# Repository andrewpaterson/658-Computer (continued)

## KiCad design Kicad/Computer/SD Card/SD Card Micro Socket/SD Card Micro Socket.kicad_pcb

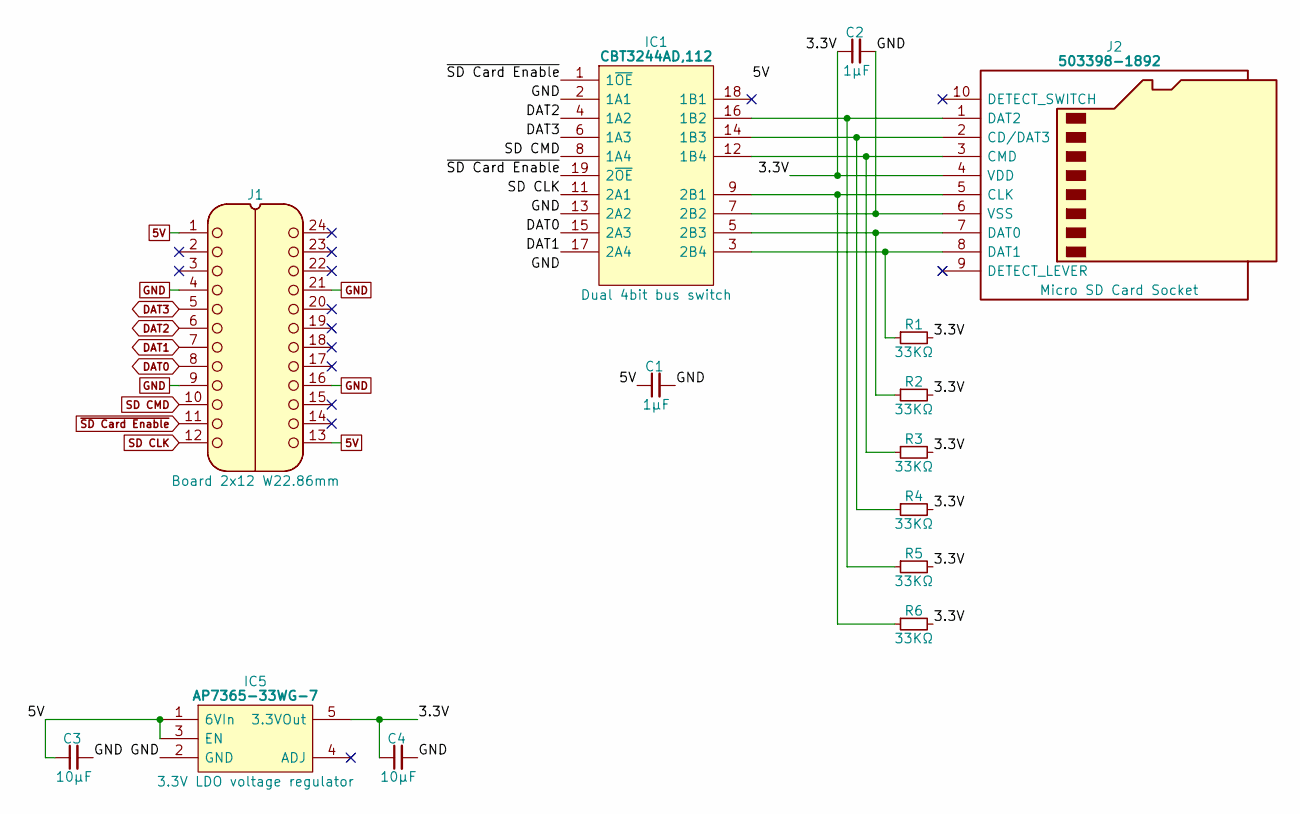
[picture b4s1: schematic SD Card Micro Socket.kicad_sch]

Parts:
C1, C2: 1μF; C_0805
C3, C4: 10µF; C_0805
IC1: CBT3244AD,112; SOIC127P1032X265-20N; Manufacturer_Part_Number CBT3244AD,112; Mouser Part Number 771-CBT3244AD
IC5: AP7365-33WG-7; SOT95P285X130-5N; Manufacturer_Part_Number AP7365-33WG-7; Mouser Part Number 621-AP7365-33WG-7
J1: Board 2x12 W22.86mm; DIP-24_Board_W22.86mm
J2: 503398-1892; Mouser2 Part Number 538-503398-1892
R1, R2, R3, R4, R5, R6: 33KΩ; R_0805

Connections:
5V: C1.1, C3.1, IC1.20 (5V), IC5.1 (6VIn), IC5.3 (EN), J1.1, J1.13
/3.3V: C2.1, C4.1, IC5.5 (3.3VOut), J2.4 (VDD), R1.2, R2.2, R3.2, R4.2, R5.2, R6.2
DAT0: IC1.15 (2A3), J1.8
DAT1: IC1.17 (2A4), J1.7
DAT2: IC1.4 (1A2), J1.6
DAT3: IC1.6 (1A3), J1.5
GND: C1.2, C2.2, C3.2, C4.2, IC1.2 (1A1), IC1.7 (2B2), IC1.10 (GND), IC1.13 (2A2), IC5.2 (GND), J1.4, J1.9, J1.16, J1.21, J2.6 (VSS)
unnamed: IC1.16 (1B2), J2.1 (DAT2), R5.1
unnamed: IC1.14 (1B3), J2.2 (CD/DAT3), R4.1
unnamed: IC1.12 (1B4), J2.3 (CMD), R3.1
unnamed: IC1.9 (2B1), J2.5 (CLK), R6.1
unnamed: IC1.5 (2B3), J2.7 (DAT0), R2.1
unnamed: IC1.3 (2B4), J2.8 (DAT1), R1.1
SD CLK: IC1.11 (2A1), J1.12
SD CMD: IC1.8 (1A4), J1.10
~SD Card Enable: IC1.1 (1~OE), IC1.19 (2~OE), J1.11

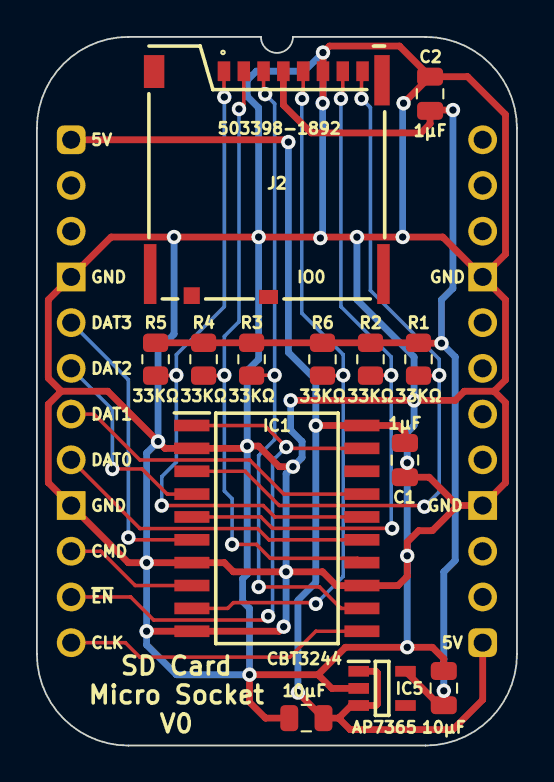
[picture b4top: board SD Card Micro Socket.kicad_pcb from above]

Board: 2 copper layers, 26.7 x 39.4 mm, 14 parts (0 on the bottom side), 16 nets.

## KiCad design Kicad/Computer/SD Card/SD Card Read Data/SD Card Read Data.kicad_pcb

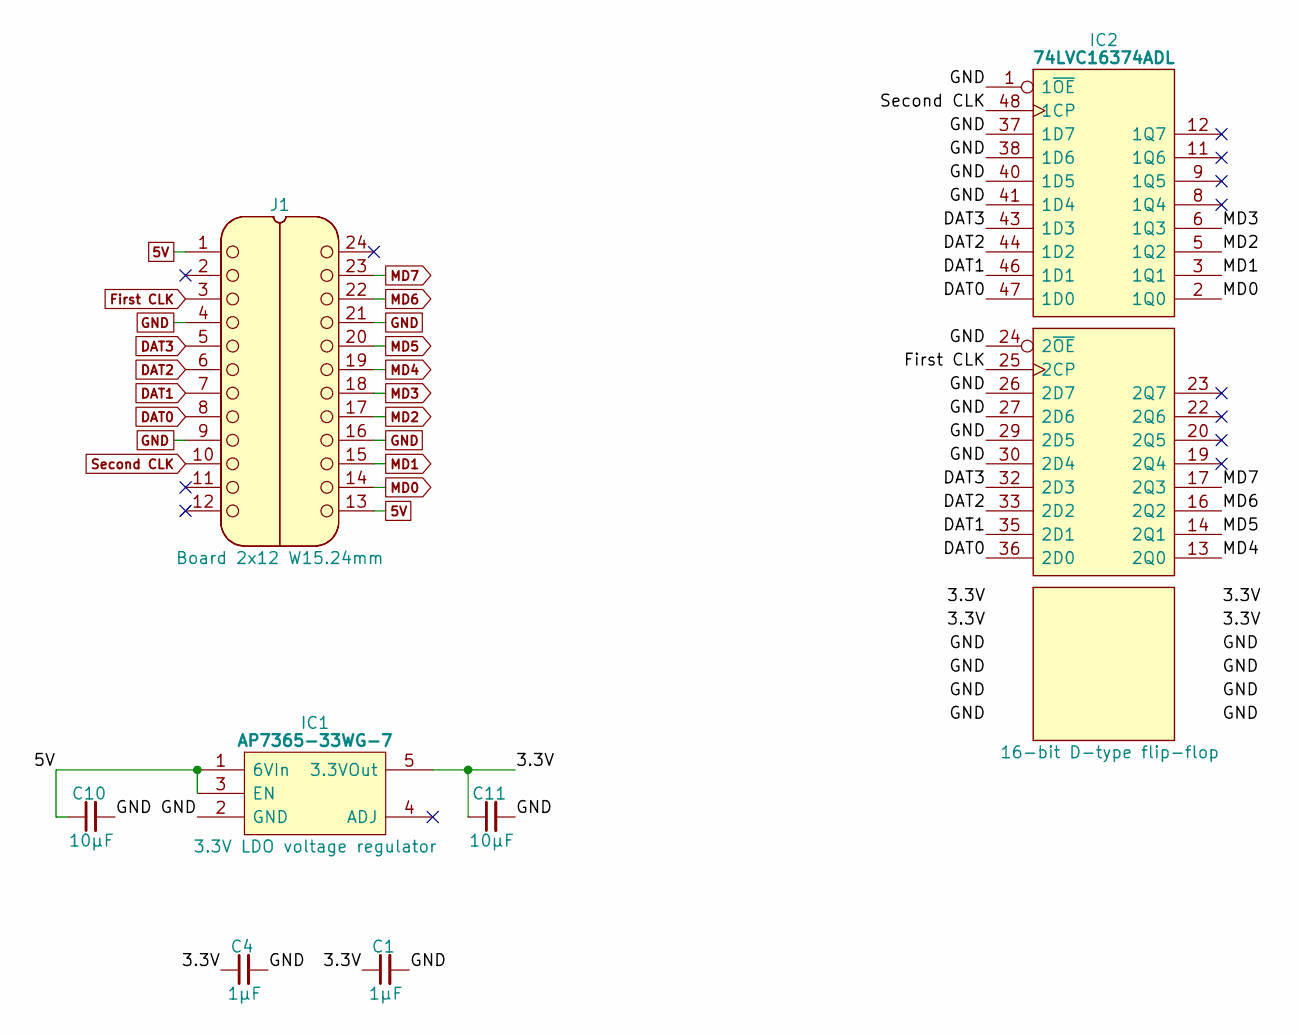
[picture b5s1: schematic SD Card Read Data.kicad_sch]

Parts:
C1, C4: 1μF; C_0805
C10, C11: 10μF; C_0805
IC1: AP7365-33WG-7; SOT95P285X130-5N; Manufacturer_Part_Number AP7365-33WG-7; Mouser Part Number 621-AP7365-33WG-7
IC2: 74LVC16374ADL; SOP64P1025X280-48N; Manufacturer_Part_Number 74LVC16374ADL; Mouser Part Number 771-74LVC16374ADL
J1: Board 2x12 W15.24mm; DIP-24_Board_W15.24mm

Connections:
5V: C10.1, IC1.1 (6VIn), IC1.3 (EN), J1.1, J1.13
/3.3V: C1.1, C4.1, C11.1, IC1.5 (3.3VOut), IC2.7 (3V), IC2.18 (3V), IC2.31 (3V), IC2.42 (3V)
DAT0: IC2.36 (2D0), IC2.47 (1D0), J1.8
DAT1: IC2.35 (2D1), IC2.46 (1D1), J1.7
DAT2: IC2.33 (2D2), IC2.44 (1D2), J1.6
DAT3: IC2.32 (2D3), IC2.43 (1D3), J1.5
First CLK: IC2.25 (2CP), J1.3
GND: C1.2, C4.2, C10.2, C11.2, IC1.2 (GND), IC2.1 (1~OE), IC2.4 (GND), IC2.10 (GND), IC2.15 (GND), IC2.21 (GND), IC2.24 (2~OE), IC2.26 (2D7), IC2.27 (2D6), IC2.28 (GND), IC2.29 (2D5), IC2.30 (2D4), IC2.34 (GND), IC2.37 (1D7), IC2.38 (1D6), IC2.39 (GND), IC2.40 (1D5), IC2.41 (1D4), IC2.45 (GND), J1.4, J1.9, J1.16, J1.21
MD0: IC2.2 (1Q0), J1.14
MD1: IC2.3 (1Q1), J1.15
MD2: IC2.5 (1Q2), J1.17
MD3: IC2.6 (1Q3), J1.18
MD4: IC2.13 (2Q0), J1.19
MD5: IC2.14 (2Q1), J1.20
MD6: IC2.16 (2Q2), J1.22
MD7: IC2.17 (2Q3), J1.23
Second CLK: IC2.48 (1CP), J1.10

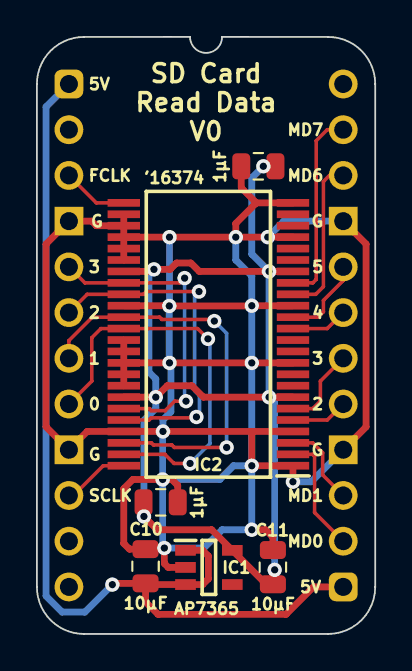
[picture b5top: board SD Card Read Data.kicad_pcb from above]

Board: 2 copper layers, 18.8 x 33.2 mm, 7 parts (0 on the bottom side), 17 nets.

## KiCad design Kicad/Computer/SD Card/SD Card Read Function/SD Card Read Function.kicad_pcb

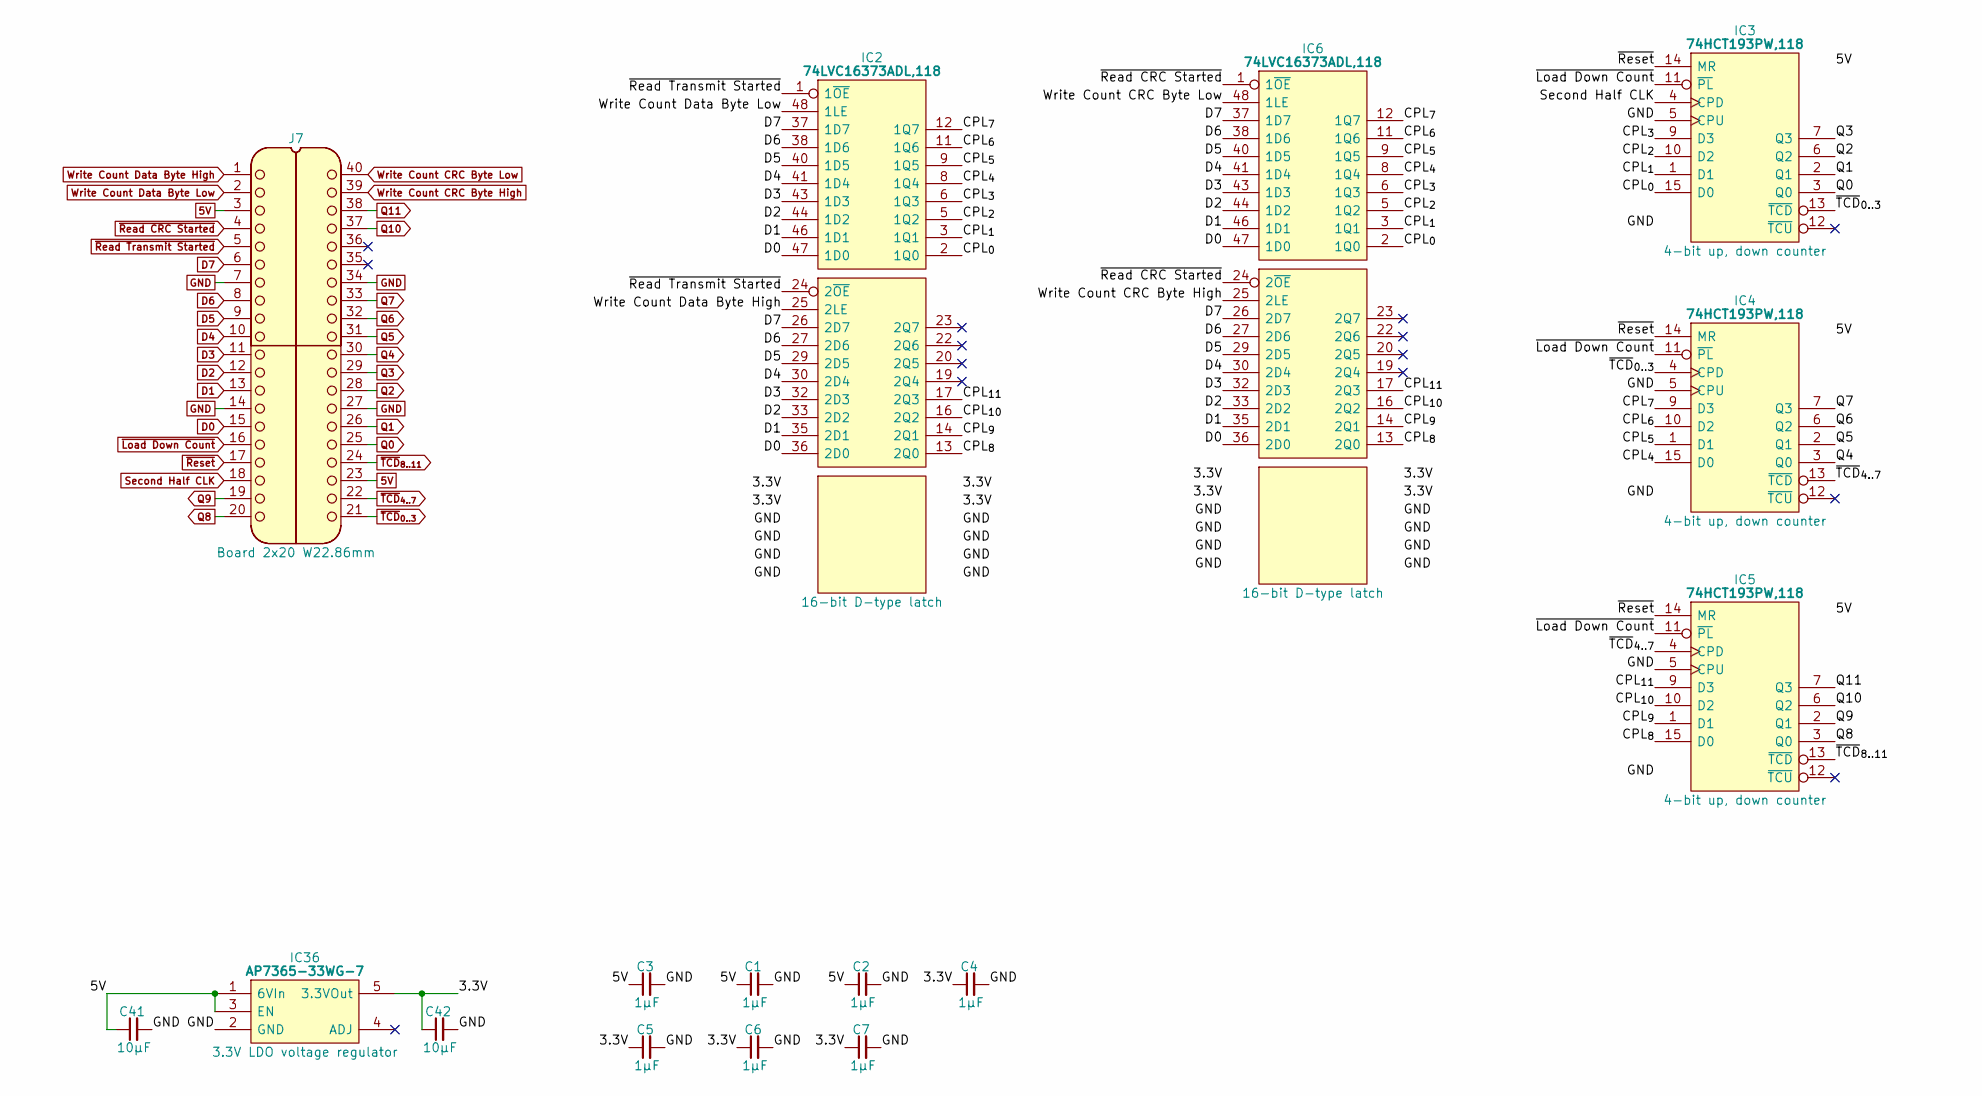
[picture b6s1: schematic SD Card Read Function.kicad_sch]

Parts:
C1, C2, C3, C4, C5, C6, C7: 1μF; C_0805
C41, C42: 10μF; C_0805
IC2, IC6: 74LVC16373ADL,118; SOP64P1025X280-48N; Mouser Part Number 771-LVC16373ADL118
IC3, IC4, IC5: 74HCT193PW,118; SOP65P640X110-16N; Manufacturer_Part_Number 74HCT193PW,118; Mouser Part Number 771-HCT193PW118
IC36: AP7365-33WG-7; SOT95P285X130-5N; Manufacturer_Part_Number AP7365-33WG-7; Mouser Part Number 621-AP7365-33WG-7
J7: Board 2x20 W22.86mm; DIP-40_Board_W22.86mm

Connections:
5V: C1.1, C2.1, C3.1, C41.1, IC3.16 (5V), IC4.16 (5V), IC5.16 (5V), IC36.1 (6VIn), IC36.3 (EN), J7.3, J7.23
/3.3V: C4.1, C5.1, C6.1, C7.1, C42.1, IC2.7 (3V), IC2.18 (3V), IC2.31 (3V), IC2.42 (3V), IC6.7 (3V), IC6.18 (3V), IC6.31 (3V), IC6.42 (3V), IC36.5 (3.3VOut)
/CPL_{0}: IC2.2 (1Q0), IC3.15 (D0), IC6.2 (1Q0)
/CPL_{1}: IC2.3 (1Q1), IC3.1 (D1), IC6.3 (1Q1)
/CPL_{2}: IC2.5 (1Q2), IC3.10 (D2), IC6.5 (1Q2)
/CPL_{3}: IC2.6 (1Q3), IC3.9 (D3), IC6.6 (1Q3)
/CPL_{4}: IC2.8 (1Q4), IC4.15 (D0), IC6.8 (1Q4)
/CPL_{5}: IC2.9 (1Q5), IC4.1 (D1), IC6.9 (1Q5)
/CPL_{6}: IC2.11 (1Q6), IC4.10 (D2), IC6.11 (1Q6)
/CPL_{7}: IC2.12 (1Q7), IC4.9 (D3), IC6.12 (1Q7)
/CPL_{8}: IC2.13 (2Q0), IC5.15 (D0), IC6.13 (2Q0)
/CPL_{9}: IC2.14 (2Q1), IC5.1 (D1), IC6.14 (2Q1)
/CPL_{10}: IC2.16 (2Q2), IC5.10 (D2), IC6.16 (2Q2)
/CPL_{11}: IC2.17 (2Q3), IC5.9 (D3), IC6.17 (2Q3)
D0: IC2.36 (2D0), IC2.47 (1D0), IC6.36 (2D0), IC6.47 (1D0), J7.15
D1: IC2.35 (2D1), IC2.46 (1D1), IC6.35 (2D1), IC6.46 (1D1), J7.13
D2: IC2.33 (2D2), IC2.44 (1D2), IC6.33 (2D2), IC6.44 (1D2), J7.12
D3: IC2.32 (2D3), IC2.43 (1D3), IC6.32 (2D3), IC6.43 (1D3), J7.11
D4: IC2.30 (2D4), IC2.41 (1D4), IC6.30 (2D4), IC6.41 (1D4), J7.10
D5: IC2.29 (2D5), IC2.40 (1D5), IC6.29 (2D5), IC6.40 (1D5), J7.9
D6: IC2.27 (2D6), IC2.38 (1D6), IC6.27 (2D6), IC6.38 (1D6), J7.8
D7: IC2.26 (2D7), IC2.37 (1D7), IC6.26 (2D7), IC6.37 (1D7), J7.6
GND: C1.2, C2.2, C3.2, C4.2, C5.2, C6.2, C7.2, C41.2, C42.2, IC2.4 (GND), IC2.10 (GND), IC2.15 (GND), IC2.21 (GND), IC2.28 (GND), IC2.34 (GND), IC2.39 (GND), IC2.45 (GND), IC3.5 (CPU), IC3.8 (GND), IC4.5 (CPU), IC4.8 (GND), IC5.5 (CPU), IC5.8 (GND), IC6.4 (GND), IC6.10 (GND), IC6.15 (GND), IC6.21 (GND), IC6.28 (GND), IC6.34 (GND), IC6.39 (GND), IC6.45 (GND), IC36.2 (GND), J7.7, J7.14, J7.27, J7.34
Q0: IC3.3 (Q0), J7.25
Q1: IC3.2 (Q1), J7.26
Q2: IC3.6 (Q2), J7.28
Q3: IC3.7 (Q3), J7.29
Q4: IC4.3 (Q0), J7.30
Q5: IC4.2 (Q1), J7.31
Q6: IC4.6 (Q2), J7.32
Q7: IC4.7 (Q3), J7.33
Q8: IC5.3 (Q0), J7.20
Q9: IC5.2 (Q1), J7.19
Q10: IC5.6 (Q2), J7.37
Q11: IC5.7 (Q3), J7.38
Second Half CLK: IC3.4 (CPD), J7.18
Write Count CRC Byte High: IC6.25 (2LE), J7.39
Write Count CRC Byte Low: IC6.48 (1LE), J7.40
Write Count Data Byte High: IC2.25 (2LE), J7.1
Write Count Data Byte Low: IC2.48 (1LE), J7.2
~Load Down Count: IC3.11 (~PL), IC4.11 (~PL), IC5.11 (~PL), J7.16
~Read CRC Started: IC6.1 (1~OE), IC6.24 (2~OE), J7.4
~Read Transmit Started: IC2.1 (1~OE), IC2.24 (2~OE), J7.5
~Reset: IC3.14 (MR), IC4.14 (MR), IC5.14 (MR), J7.17
~TCD_{0..3}: IC3.13 (~TCD), IC4.4 (CPD), J7.21
~TCD_{4..7}: IC4.13 (~TCD), IC5.4 (CPD), J7.22
~TCD_{8..11}: IC5.13 (~TCD), J7.24

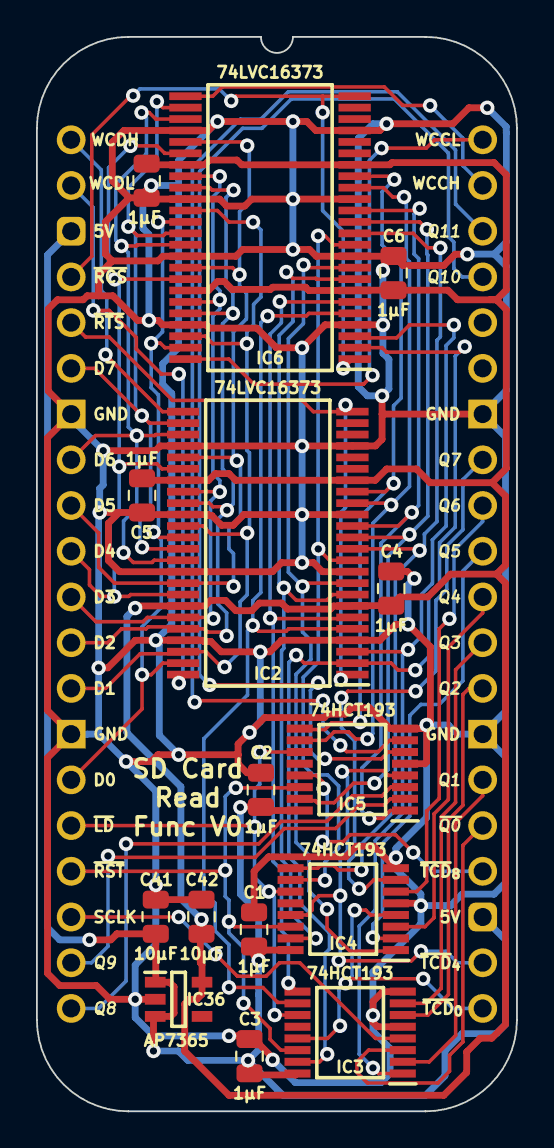
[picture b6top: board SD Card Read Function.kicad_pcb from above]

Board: 2 copper layers, 26.7 x 59.7 mm, 16 parts (0 on the bottom side), 47 nets.

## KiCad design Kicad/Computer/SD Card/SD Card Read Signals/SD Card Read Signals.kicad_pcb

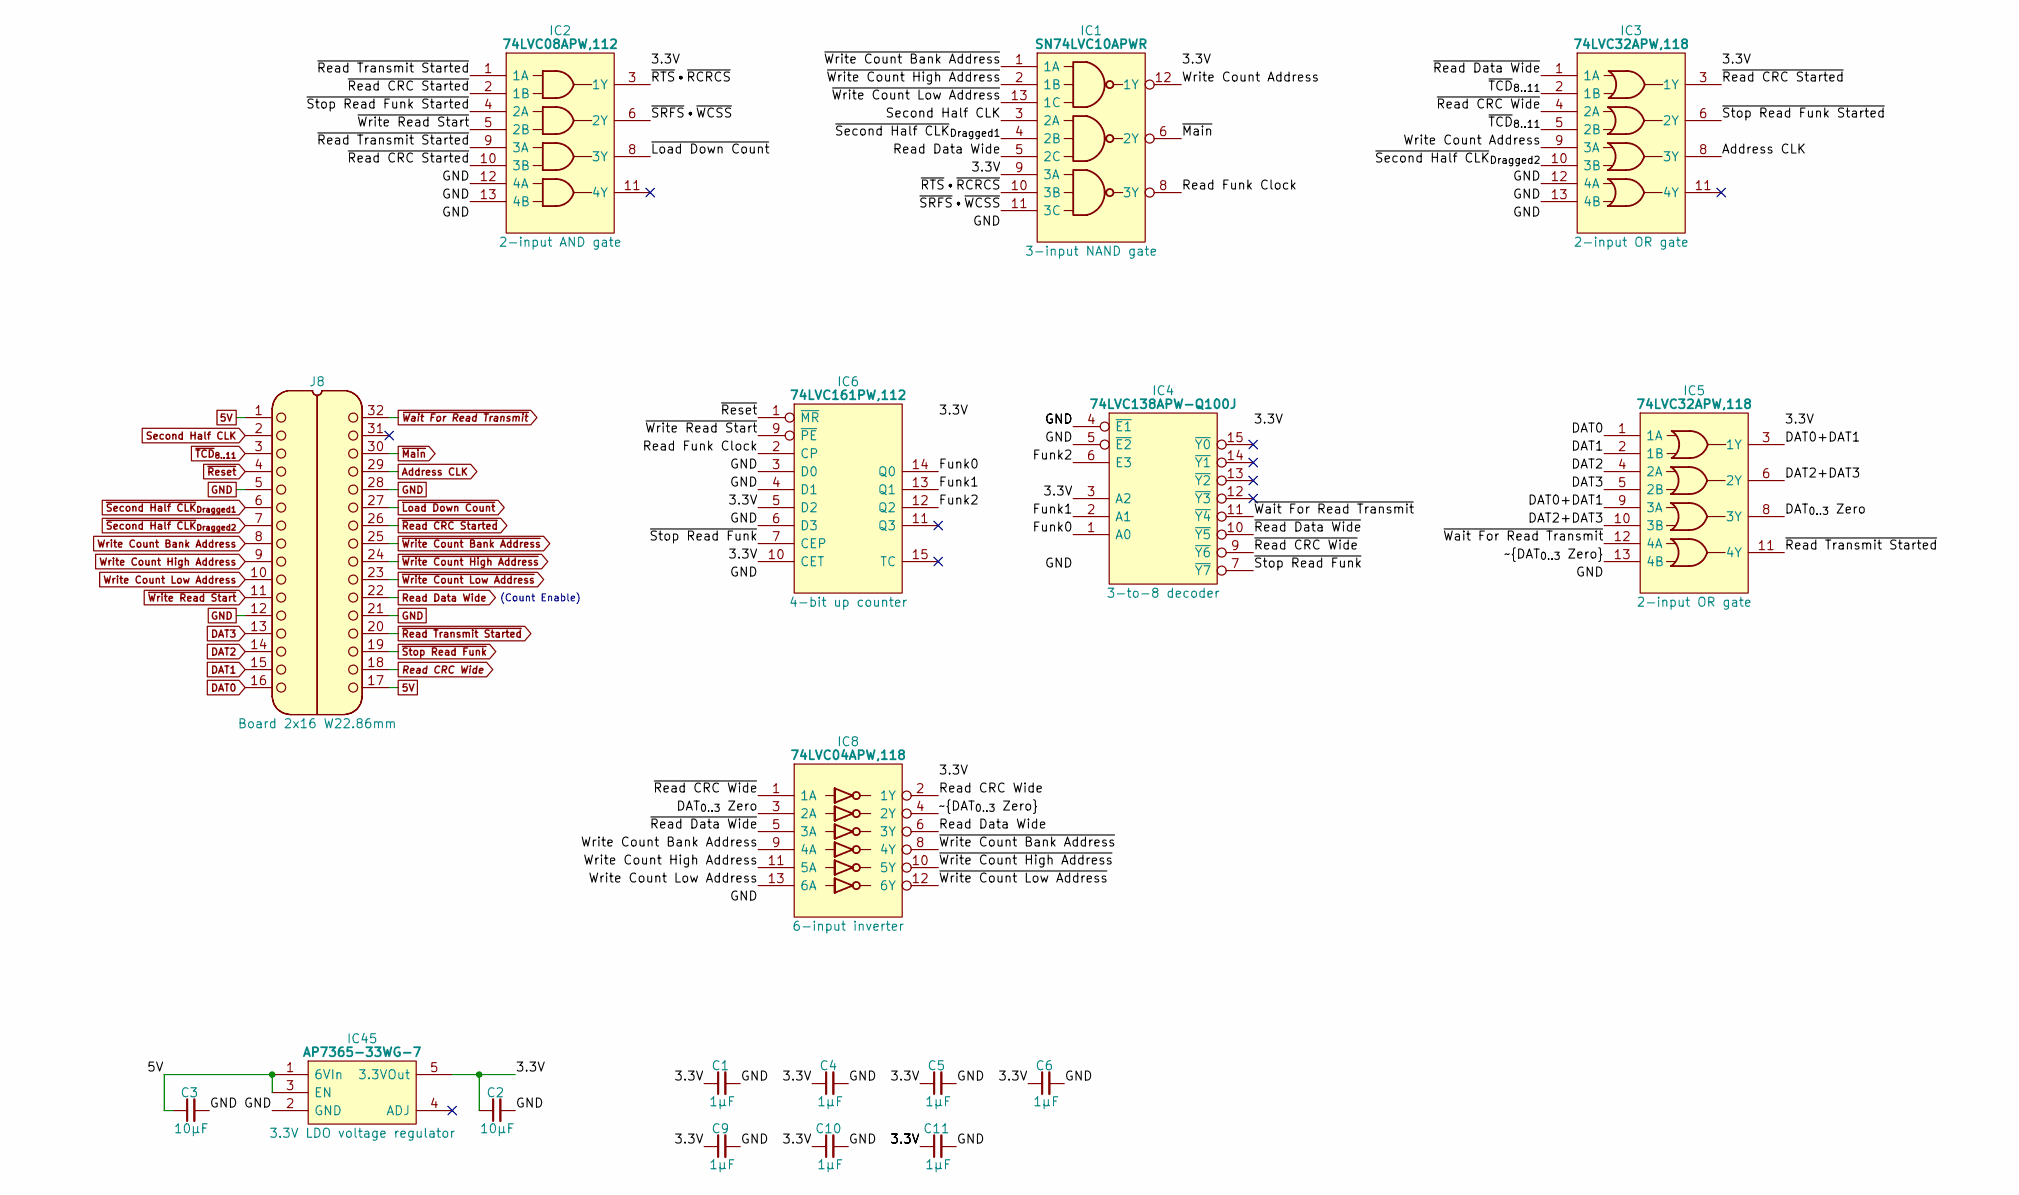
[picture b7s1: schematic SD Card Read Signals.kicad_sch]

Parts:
C1, C4, C5, C6, C9, C10, C11: 1μF; C_0805
C2, C3: 10μF; C_0805
IC1: SN74LVC10APWR; SOP65P640X120-14N; Manufacturer_Part_Number SN74LVC10APWR; Mouser Part Number 595-SN74LVC10APWR
IC2: 74LVC08APW,112; SOP65P640X110-14N; Manufacturer_Part_Number 74LVC08APW,112; Mouser Part Number 771-74LVC08APW
IC3, IC5: 74LVC32APW,118; SOP65P640X110-14N; Manufacturer_Part_Number 74LVC32APW,118; Mouser Part Number 771-74LVC32APW-T
IC4: 74LVC138APW-Q100J; SOP65P640X110-16N; Mouser Part Number 771-74LVC138APWQ100J
IC6: 74LVC161PW,112; SOP65P640X110-16N; Mouser Part Number 771-LVC161PW112
IC8: 74LVC04APW,118; SOP65P640X110-14N; Manufacturer_Part_Number 74LVC04APW,118; Mouser Part Number 771-74LVC04APW-T
IC45: AP7365-33WG-7; SOT95P285X130-5N; Manufacturer_Part_Number AP7365-33WG-7; Mouser Part Number 621-AP7365-33WG-7
J8: Board 2x16 W22.86mm; DIP-32_Board_W22.86mm

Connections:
5V: C3.1, IC45.1 (6VIn), IC45.3 (EN), J8.1, J8.17
/3.3V: C1.1, C2.1, C4.1, C5.1, C6.1, C9.1, C10.1, C11.1, IC1.9 (3A), IC1.14 (3V), IC2.14 (3V), IC3.14 (3V), IC4.3 (A2), IC4.16 (3V), IC5.14 (3V), IC6.5 (D2), IC6.10 (CET), IC6.16 (3V), IC8.14 (3V), IC45.5 (3.3VOut)
/DAT0+DAT1: IC5.3 (1Y), IC5.9 (3A)
/DAT2+DAT3: IC5.6 (2Y), IC5.10 (3B)
/DAT_{0..3} Zero: IC5.8 (3Y), IC8.3 (2A)
/Funk0: IC4.1 (A0), IC6.14 (Q0)
/Funk1: IC4.2 (A1), IC6.13 (Q1)
/Funk2: IC4.6 (E3), IC6.12 (Q2)
/Read Funk Clock: IC1.8 (3Y), IC6.2 (CP)
/Write Count Address: IC1.12 (1Y), IC3.9 (3A)
/~DAT_{0..3 Zero}: IC5.13 (4B), IC8.4 (2Y)
/~RTS•~RCRCS: IC1.10 (3B), IC2.3 (1Y)
/~Read CRC Wide: IC3.4 (2A), IC4.9 (~Y6), IC8.1 (1A)
/~Read Data Wide: IC3.1 (1A), IC4.10 (~Y5), IC8.5 (3A)
/~SRFS•~WCSS: IC1.11 (3C), IC2.6 (2Y)
/~Stop Read Funk Started: IC2.4 (2A), IC3.6 (2Y)
Address CLK: IC3.8 (3Y), J8.29
DAT0: IC5.1 (1A), J8.16
DAT1: IC5.2 (1B), J8.15
DAT2: IC5.4 (2A), J8.14
DAT3: IC5.5 (2B), J8.13
GND: C1.2, C2.2, C3.2, C4.2, C5.2, C6.2, C9.2, C10.2, C11.2, IC1.7 (GND), IC2.7 (GND), IC2.12 (4A), IC2.13 (4B), IC3.7 (GND), IC3.12 (4A), IC3.13 (4B), IC4.4 (~E1), IC4.5 (~E2), IC4.8 (GND), IC5.7 (GND), IC6.3 (D0), IC6.4 (D1), IC6.6 (D3), IC6.8 (GND), IC8.7 (GND), IC45.2 (GND), J8.5, J8.12, J8.21, J8.28
Read CRC Wide: IC8.2 (1Y), J8.18
Read Data Wide: IC1.5 (2C), IC8.6 (3Y), J8.22
Second Half CLK: IC1.3 (2A), J8.2
Write Count Bank Address: IC8.9 (4A), J8.8
Write Count High Address: IC8.11 (5A), J8.9
Write Count Low Address: IC8.13 (6A), J8.10
~Load Down Count: IC2.8 (3Y), J8.27
~Main: IC1.6 (2Y), J8.30
~Read CRC Started: IC2.2 (1B), IC2.10 (3B), IC3.3 (1Y), J8.26
~Read Transmit Started: IC2.1 (1A), IC2.9 (3A), IC5.11 (4Y), J8.20
~Reset: IC6.1 (~MR), J8.4
~Second Half CLK_{Dragged1}: IC1.4 (2B), J8.6
~Second Half CLK_{Dragged2}: IC3.10 (3B), J8.7
~Stop Read Funk: IC4.7 (~Y7), IC6.7 (CEP), J8.19
~TCD_{8..11}: IC3.2 (1B), IC3.5 (2B), J8.3
~Wait For Read Transmit: IC4.11 (~Y4), IC5.12 (4A), J8.32
~Write Count Bank Address: IC1.1 (1A), IC8.8 (4Y), J8.25
~Write Count High Address: IC1.2 (1B), IC8.10 (5Y), J8.24
~Write Count Low Address: IC1.13 (1C), IC8.12 (6Y), J8.23
~Write Read Start: IC2.5 (2B), IC6.9 (~PE), J8.11

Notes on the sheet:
(Count Enable)

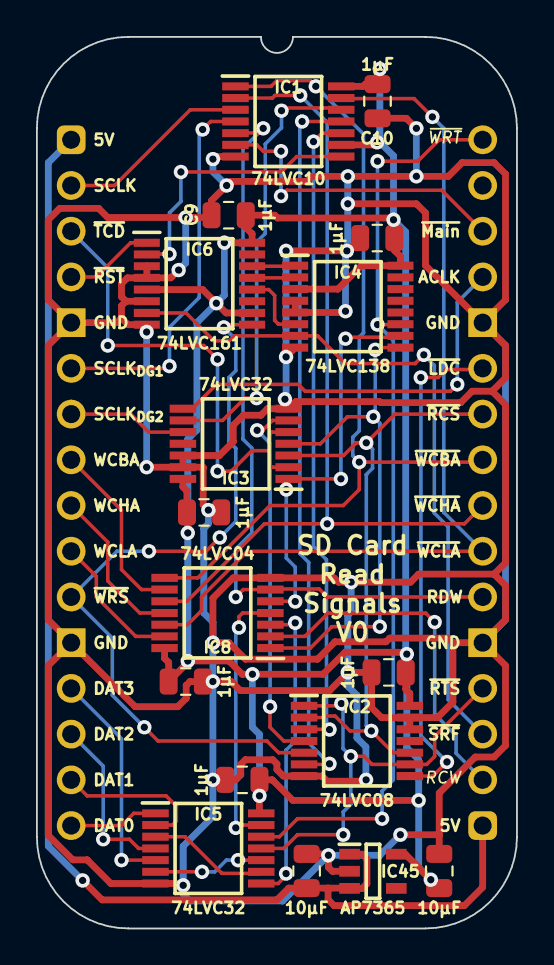
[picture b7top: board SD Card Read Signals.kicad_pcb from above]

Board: 2 copper layers, 26.7 x 49.5 mm, 18 parts (0 on the bottom side), 42 nets.

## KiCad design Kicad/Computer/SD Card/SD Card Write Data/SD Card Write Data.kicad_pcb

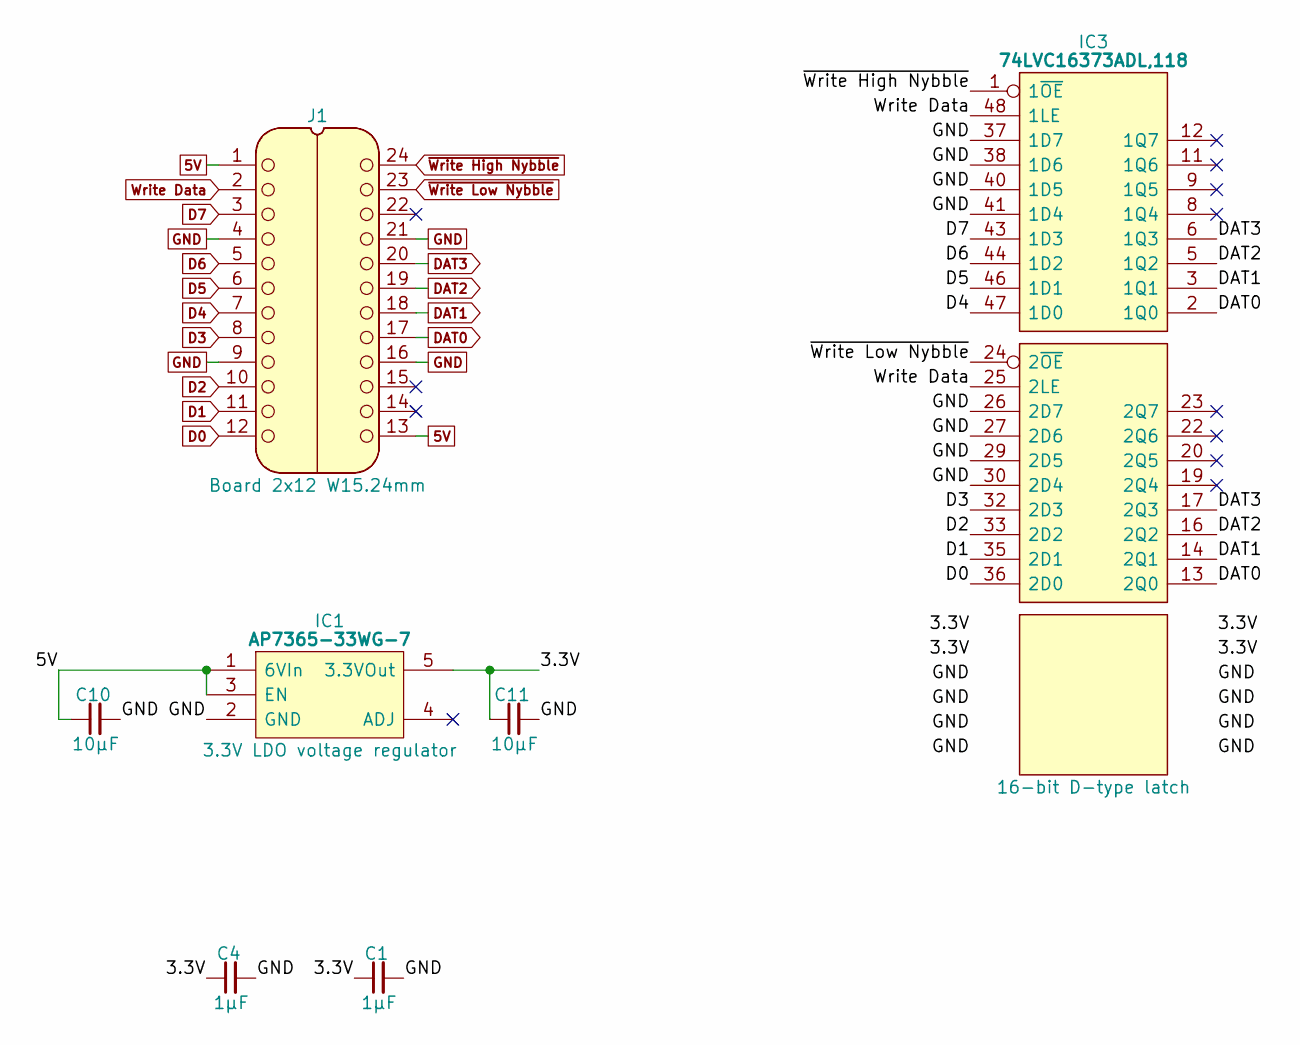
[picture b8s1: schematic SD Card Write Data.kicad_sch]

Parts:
C1, C4: 1μF; C_0805
C10, C11: 10μF; C_0805
IC1: AP7365-33WG-7; SOT95P285X130-5N; Manufacturer_Part_Number AP7365-33WG-7; Mouser Part Number 621-AP7365-33WG-7
IC3: 74LVC16373ADL,118; SOP64P1025X280-48N; Mouser Part Number 771-LVC16373ADL118
J1: Board 2x12 W15.24mm; DIP-24_Board_W15.24mm

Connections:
5V: C10.1, IC1.1 (6VIn), IC1.3 (EN), J1.1, J1.13
/3.3V: C1.1, C4.1, C11.1, IC1.5 (3.3VOut), IC3.7 (3V), IC3.18 (3V), IC3.31 (3V), IC3.42 (3V)
D0: IC3.36 (2D0), J1.12
D1: IC3.35 (2D1), J1.11
D2: IC3.33 (2D2), J1.10
D3: IC3.32 (2D3), J1.8
D4: IC3.47 (1D0), J1.7
D5: IC3.46 (1D1), J1.6
D6: IC3.44 (1D2), J1.5
D7: IC3.43 (1D3), J1.3
DAT0: IC3.2 (1Q0), IC3.13 (2Q0), J1.17
DAT1: IC3.3 (1Q1), IC3.14 (2Q1), J1.18
DAT2: IC3.5 (1Q2), IC3.16 (2Q2), J1.19
DAT3: IC3.6 (1Q3), IC3.17 (2Q3), J1.20
GND: C1.2, C4.2, C10.2, C11.2, IC1.2 (GND), IC3.4 (GND), IC3.10 (GND), IC3.15 (GND), IC3.21 (GND), IC3.26 (2D7), IC3.27 (2D6), IC3.28 (GND), IC3.29 (2D5), IC3.30 (2D4), IC3.34 (GND), IC3.37 (1D7), IC3.38 (1D6), IC3.39 (GND), IC3.40 (1D5), IC3.41 (1D4), IC3.45 (GND), J1.4, J1.9, J1.16, J1.21
Write Data: IC3.25 (2LE), IC3.48 (1LE), J1.2
~Write High Nybble: IC3.1 (1~OE), J1.24
~Write Low Nybble: IC3.24 (2~OE), J1.23

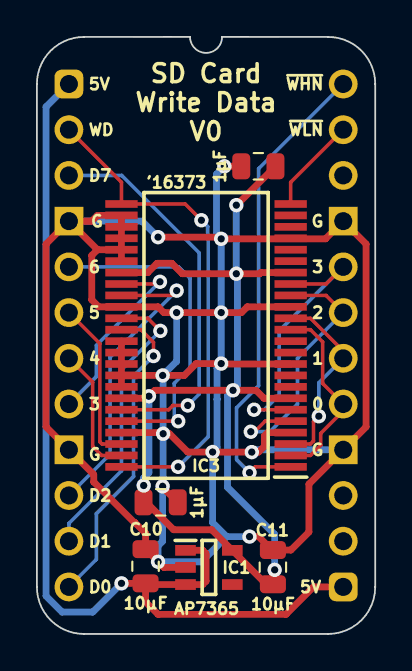
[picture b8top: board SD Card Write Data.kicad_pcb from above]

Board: 2 copper layers, 18.8 x 33.2 mm, 7 parts (0 on the bottom side), 18 nets.
